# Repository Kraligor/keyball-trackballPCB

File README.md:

# Fork Info

This fork includes reverse-engineered KiCAD files and BOM for the trackball PCB. Resistors and caps are 0603/1608, connector is 2.54. The connector layout and component values are identical to the the original PCB, footprints differ as it's supposed to be hand-soldered, so the packages are bigger.

# Keyball Series

Keyball series is keyboard family which have 100% track ball.

Keyboards in the family are:

* Available
    * Keyball39: split + 39 keys + a track ball
    * Keyball44: split + 44 keys + a track ball
    * Keyball61: split + 61 keys + a track ball
* Unavailable
    * Keyball46 (first one!)
    * One47

## Where to Buy

|Keyboard   |Yushakobo / 遊舎工房                       |Shirogane Lab / 白金ラボ                                   |
|-----------|-------------------------------------------|-----------------------------------------------------------|
|Keyball39  |<https://shop.yushakobo.jp/products/5357>  |<https://shirogane-lab.net/items/64b8f8693ee3fd0045280190> |
|Keyball44  |<https://shop.yushakobo.jp/products/8337>  |<https://shirogane-lab.net/items/64b7a006eb6dbe00346cd0c5> |
|Keyball61  |<https://shop.yushakobo.jp/products/5358>  |<https://shirogane-lab.net/items/64b8ed191435c1002bc4cd30> |

## Build Guide

*   Keyball39:
    [English/英語](/keyball39/doc/rev1/buildguide_en.md),
    [日本語/Japanese (ピンヘッダ版)](./keyball39/doc/rev1/buildguide_jp.md),
    [日本語/Japanese (コンスルー版)](./keyball39/doc/rev1/buildguide_jp_conth.md)
*   Keyball44: ~~English/英語~~ (Sorry, unavailable),
    [日本語/Japanese (ピンヘッダ版)](./keyball44/doc/rev1/buildguide_jp.md),
    [日本語/Japanese (コンスルー版)](./keyball44/doc/rev1/buildguide_jp_conth.md)
*   Keyball46:
    [English/英語](./keyball46/doc/rev1/buildguide_en.md),
    [日本語/Japanese](./keyball46/doc/rev1/buildguide_jp.md)
*   Keyball61:
    [English/英語](./keyball61/doc/rev1/buildguide_en.md),
    [日本語/Japanese (ピンヘッダ版)](./keyball61/doc/rev1/buildguide_jp.md),
    [日本語/Japanese (コンスルー版)](./keyball61/doc/rev1/buildguide_jp_conth.md)

## Firmware

See [document for firmware source code](./qmk_firmware/keyboards/keyball/readme.md).

### Pre-compiled Firmwares

(TO BE DOCUMENTED)

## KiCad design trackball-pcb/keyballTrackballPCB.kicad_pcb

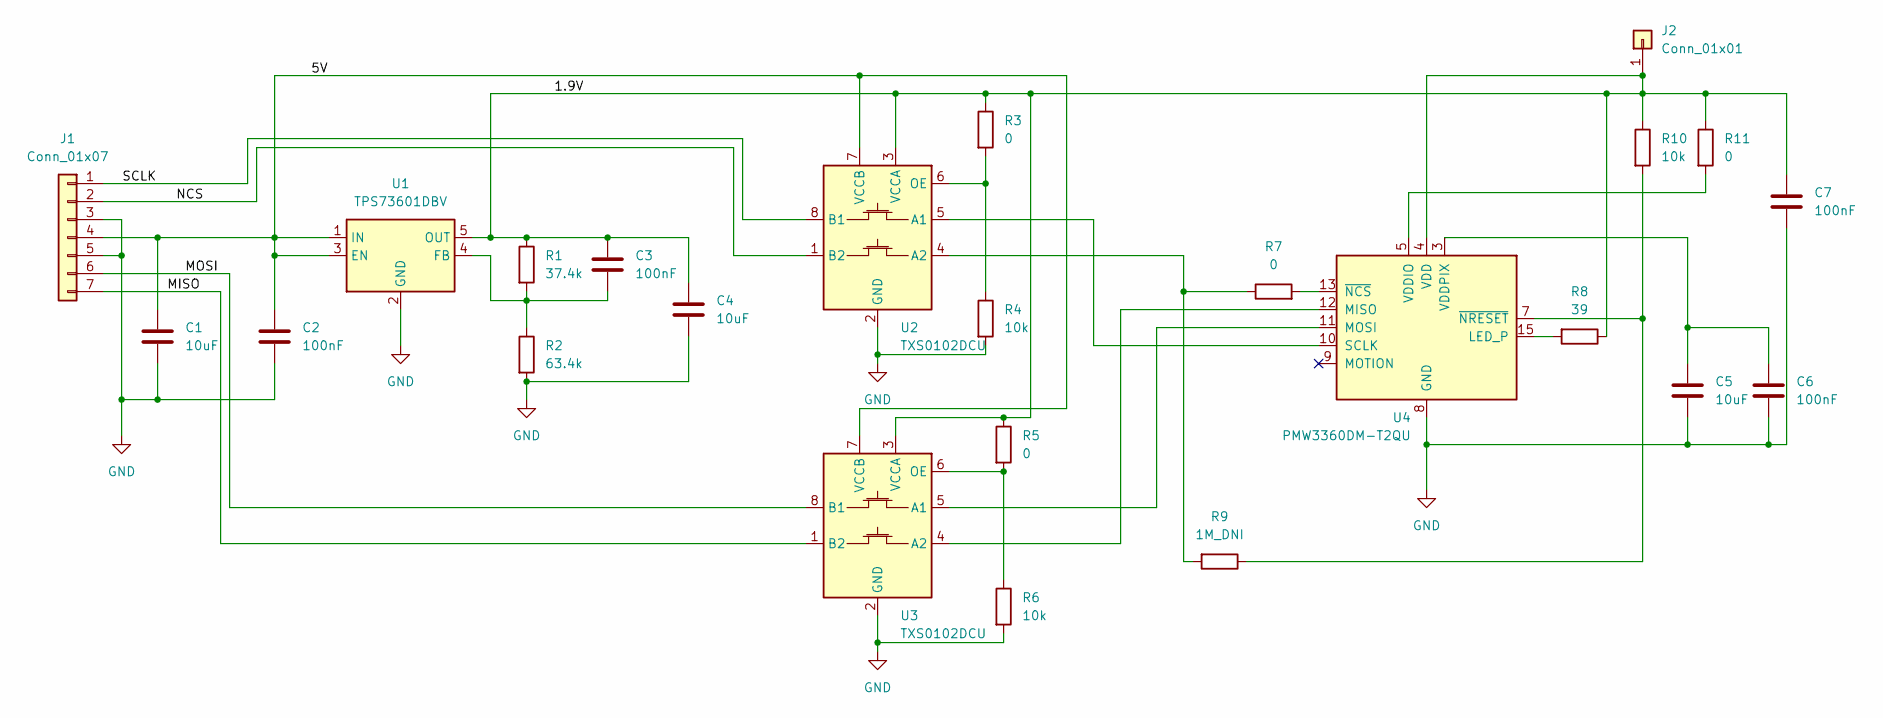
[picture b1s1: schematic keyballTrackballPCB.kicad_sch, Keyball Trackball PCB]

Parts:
C1, C4, C5: 10uF; C_0603_1608Metric_Pad1.08x0.95mm_HandSolder
C2, C3, C6, C7: 100nF; C_0603_1608Metric_Pad1.08x0.95mm_HandSolder
J1: Conn_01x07; PinHeader_1x07_P2.54mm_Vertical
J2: Conn_01x01; PinHeader_1x01_P2.54mm_Vertical
R1: 37.4k; R_0603_1608Metric_Pad0.98x0.95mm_HandSolder
R2: 63.4k; R_0603_1608Metric_Pad0.98x0.95mm_HandSolder
R3, R5, R7, R11: 0; R_0603_1608Metric_Pad0.98x0.95mm_HandSolder
R4, R6, R10: 10k; R_0603_1608Metric_Pad0.98x0.95mm_HandSolder
R8: 39; R_0603_1608Metric_Pad0.98x0.95mm_HandSolder
R9: 1M_DNI; R_0603_1608Metric_Pad0.98x0.95mm_HandSolder
U1: TPS73601DBV; SOT-23-5
U2, U3: TXS0102DCU; VSSOP-8_2.3x2mm_P0.5mm
U4: PMW3360DM-T2QU

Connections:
/1.9V: C3.1, C4.1, C7.1, J2.1, R1.1, R3.1, R5.1, R8.1, R10.1, R11.1, U1.5 (OUT), U2.3 (VCCA), U3.3 (VCCA), U4.4 (VDD)
/5V: C1.1, C2.1, J1.4, U1.1 (IN), U1.3 (EN), U2.7 (VCCB), U3.7 (VCCB)
/MISO: J1.7, U3.1 (B2)
/MOSI: J1.6, U3.8 (B1)
/NCS: J1.2, U2.1 (B2)
/SCLK: J1.1, U2.8 (B1)
GND: C1.2, C2.2, C4.2, C5.2, C6.2, C7.2, J1.3, J1.5, R2.2, R4.2, R6.2, U1.2 (GND), U2.2 (GND), U3.2 (GND), U4.8 (GND)
unnamed: C3.2, R1.2, R2.1, U1.4 (FB)
unnamed: U2.5 (A1), U4.10 (SCLK)
unnamed: R7.1, R9.2, U2.4 (A2)
unnamed: R3.2, R4.1, U2.6 (OE)
unnamed: U3.5 (A1), U4.11 (MOSI)
unnamed: U3.4 (A2), U4.12 (MISO)
unnamed: R5.2, R6.1, U3.6 (OE)
unnamed: R8.2, U4.15 (LED_P)
unnamed: R11.2, U4.5 (VDDIO)
unnamed: C5.1, C6.1, U4.3 (VDDPIX)
unnamed: R7.2, U4.13 (~NCS)
unnamed: R9.1, R10.2, U4.7 (~NRESET)

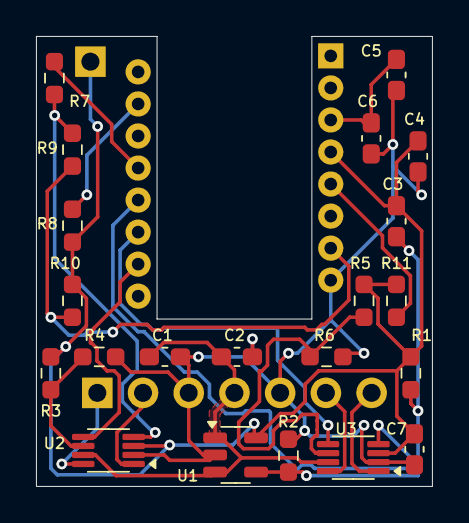
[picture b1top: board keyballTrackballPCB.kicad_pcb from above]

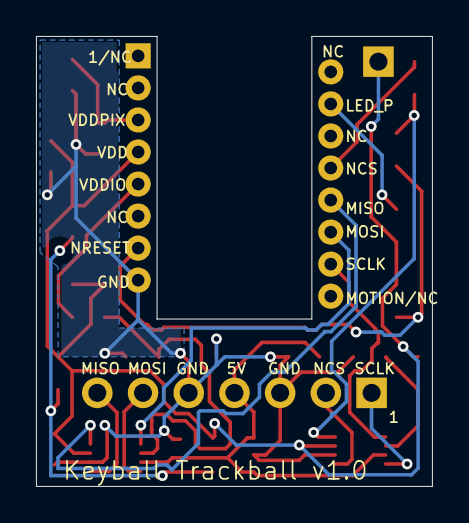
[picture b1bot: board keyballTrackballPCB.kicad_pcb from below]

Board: 2 copper layers, 22.0 x 25.0 mm, 24 parts (3 on the bottom side), 19 nets.

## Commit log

2025-11-21 Uploading KiCAD files
2025-11-21 add BOM
